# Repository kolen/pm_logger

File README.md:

# Firmware

## Building firmware

* Install [platformio](https://platformio.org)
* Run `pio run` in root dir

To flash firmware:

* Run `pio run -t upload`

## Running tests

* Install native C++ toolchain (for your system, not for cross-compilation), clang or gcc
* Install [meson](https://mesonbuild.com/) build system and [ninja](https://ninja-build.org/) low-level build system
* Run `meson builddir` in the root directory of project
* Change dir to `builddir` and run `ninja test`

## Using native simulator

Native simulator runs on unix-like systems. It runs the same main loop
as actual app and has networking, but instead of real sensor readings,
it reads the same value each time. Simulated time is 60x faster that
real time, i.e. each simulated hour is a real minute.

To build native simulator, use the same steps as for tests, but just
run `ninja`. It builds `pm_sensor_fake` executable in `builddir`.

# Logging node

## Building and installing

* Install Rust and Cargo
* Run `cargo build` in `logging_node` directory
* Install [Diesel](http://diesel.rs/) cli: `cargo install diesel_cli
  --no-default-features --features sqlite` (by default, all features
  are installed, which require client libs for postgresql and mysql,
  which are not needed for logging node)
* Run schema migration: `diesel migration run`
* Run built binary directly or with `cargo run`

# Homebridge plugin

## Installing

* Install node.js
* Install and configure [homebridge](https://github.com/nfarina/homebridge)
* Run `npm install -g` in `homebridge-pm-sensor` dir
* Add accessory to homebridge:

  ```json
      "accessories": [
          {
              "accessory": "PMSensor",
              "name": "pm_sensor"
          }
      ]
  ```

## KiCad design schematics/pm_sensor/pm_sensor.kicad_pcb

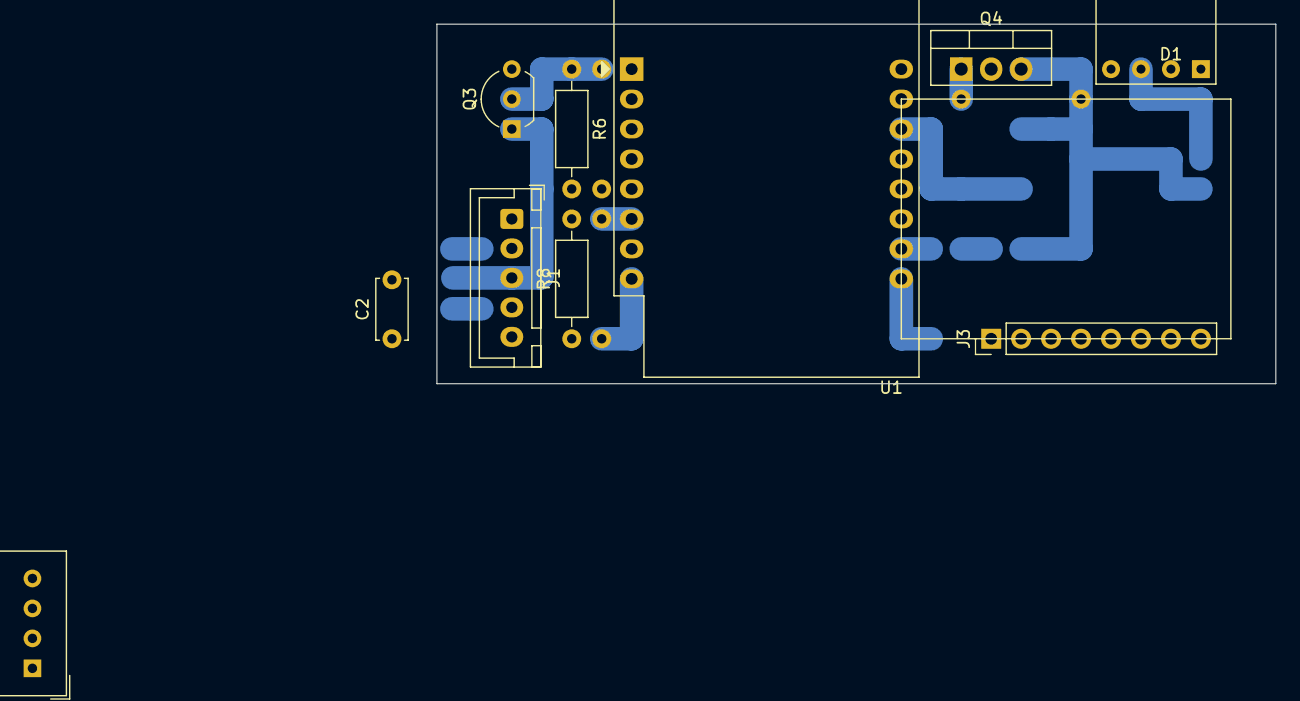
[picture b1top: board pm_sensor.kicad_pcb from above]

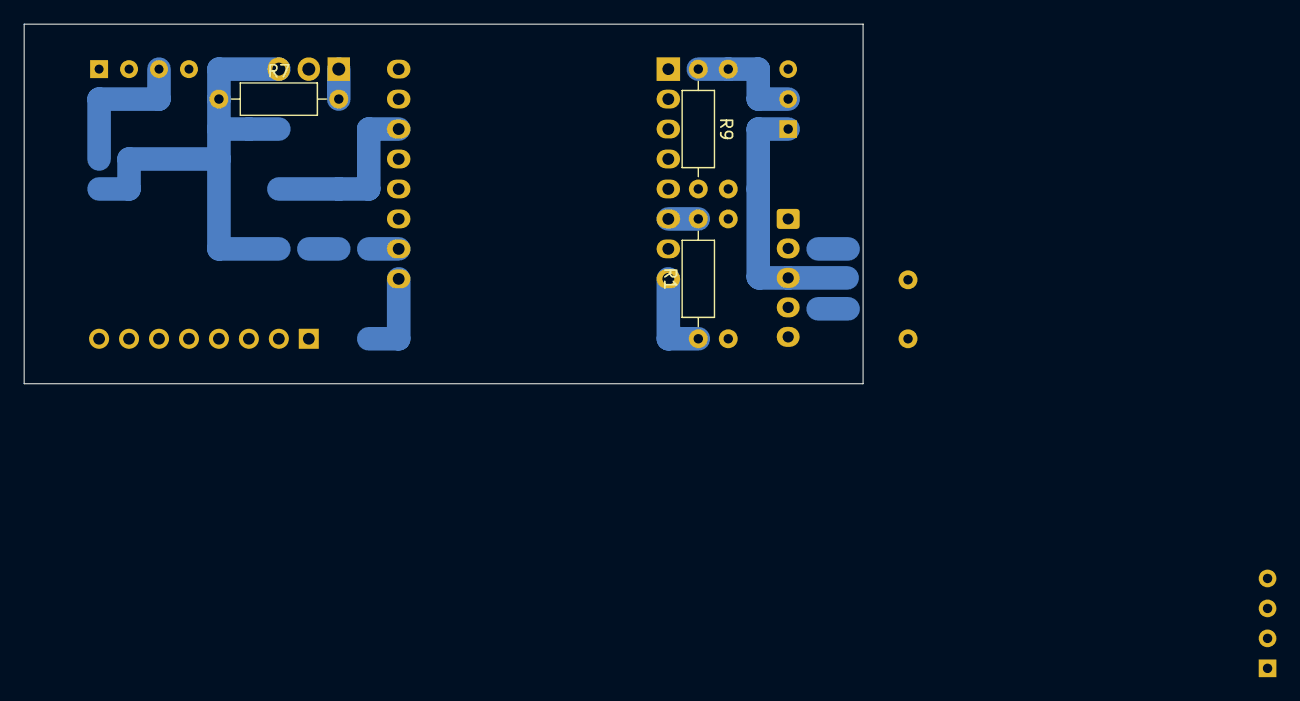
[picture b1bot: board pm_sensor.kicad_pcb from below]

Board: 2 copper layers, 71.1 x 30.5 mm, 13 parts (3 on the bottom side), 14 nets.

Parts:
C2: 100nF; C_Disc_D5.0mm_W2.5mm_P5.00mm
D1: BMP180_breakout; BMP180_Breakout
J1: sds011_conn; JST_XH_B5B-XH-A_1x05_P2.50mm_Vertical
J3: display_conn; PinHeader_1x08_P2.54mm_Vertical
Q3: 2N7000TA; TO-92_Inline_Wide
Q4: IRF9510; TO-220-3_Vertical
R1, R7, R9: 10k; R_Axial_DIN0207_L6.3mm_D2.5mm_P10.16mm_Horizontal
R6, R8: 300; R_Axial_DIN0207_L6.3mm_D2.5mm_P10.16mm_Horizontal
U1: WeMos_D1_mini; WEMOS_D1_mini_light
U2: DHT22; Aosong_DHT11_5.5x12.0_P2.54mm

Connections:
+3V3: D1.4, J3.6, R1.1, U1.8, U2.1
+5V: Q4.3, R7.1, U1.9
GND: C2.2, D1.3, J1.3, J3.2, J3.8, Q3.1, R9.2, U1.10, U2.4
unnamed: Q3.2, R6.1, R9.1
unnamed: Q3.3, R8.2
unnamed: Q4.1, R7.2, R8.1
dht_data: R1.2, U1.6, U2.2
rst: J3.1, U1.1
scl_3v: D1.2, U1.13
sda_3v: D1.1, U1.14
sds_rx: J1.1, U1.4
sds_switch: R6.2, U1.3
sds_tx: J1.2, U1.5
sds_vcc: C2.1, J1.4, Q4.2

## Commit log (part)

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2019-03-24 Fix matching in Display impl for QueryCharacteristic
2019-03-24 Add LOGGER_HOST to .env
2019-03-26 Add homebridge module
2019-04-01 Return result from update_characteristic
2019-05-20 Add schematics
2019-05-20 Bump container version in circleci
2019-05-21 Add delay after turning on SDS011 (check if necessary)
2019-06-18 Ignore fp-info-cache
2019-07-25 Build & test logging_node on CI (#19)
2019-07-25 Bump memchr from 2.2.0 to 2.2.1 in /logging_node (#18)
    Bumps [memchr](https://github.com/BurntSushi/rust-memchr) from 2.2.0 to 2.2.1.
    - [Release notes](https://github.com/BurntSushi/rust-memchr/releases)
    - [Commits](https://github.com/BurntSushi/rust-memchr/compare/2.2.0...2.2.1)
2019-07-25 Bump dotenv from 0.13.0 to 0.14.1 in /logging_node (#16)
    Bumps [dotenv](https://github.com/dotenv-rs/dotenv) from 0.13.0 to 0.14.1.
    - [Release notes](https://github.com/dotenv-rs/dotenv/releases)
    - [Changelog](https://github.com/dotenv-rs/dotenv/blob/master/CHANGELOG.md)
    - [Commits](https://github.com/dotenv-rs/dotenv/compare/v0.13.0...v0.14.1)
2019-07-25 Bump byteorder from 1.3.1 to 1.3.2 in /logging_node
    Bumps [byteorder](https://github.com/BurntSushi/byteorder) from 1.3.1 to 1.3.2.
    - [Release notes](https://github.com/BurntSushi/byteorder/releases)
    - [Changelog](https://github.com/BurntSushi/byteorder/blob/master/CHANGELOG.md)
    - [Commits](https://github.com/BurntSushi/byteorder/compare/1.3.1...1.3.2)
2019-07-25 Bump autocfg from 0.1.2 to 0.1.5 in /logging_node
    Bumps [autocfg](https://github.com/cuviper/autocfg) from 0.1.2 to 0.1.5.
    - [Release notes](https://github.com/cuviper/autocfg/releases)
    - [Commits](https://github.com/cuviper/autocfg/commits)
2019-07-25 Bump syn from 0.15.29 to 0.15.42 in /logging_node (#23)
    Bumps [syn](https://github.com/dtolnay/syn) from 0.15.29 to 0.15.42.
    - [Release notes](https://github.com/dtolnay/syn/releases)
    - [Commits](https://github.com/dtolnay/syn/compare/0.15.29...0.15.42)
2019-07-25 Bump num-traits from 0.2.6 to 0.2.8 in /logging_node (#25)
    Bumps [num-traits](https://github.com/rust-num/num-traits) from 0.2.6 to 0.2.8.
    - [Release notes](https://github.com/rust-num/num-traits/releases)
    - [Changelog](https://github.com/rust-num/num-traits/blob/master/RELEASES.md)
    - [Commits](https://github.com/rust-num/num-traits/compare/num-traits-0.2.6...num-traits-0.2.8)
2019-07-25 Bump cc from 1.0.31 to 1.0.38 in /logging_node (#26)
    Bumps [cc](https://github.com/alexcrichton/cc-rs) from 1.0.31 to 1.0.38.
    - [Release notes](https://github.com/alexcrichton/cc-rs/releases)
    - [Commits](https://github.com/alexcrichton/cc-rs/compare/1.0.31...1.0.38)
2019-07-25 Bump ucd-util from 0.1.3 to 0.1.5 in /logging_node
    Bumps [ucd-util](https://github.com/BurntSushi/ucd-generate) from 0.1.3 to 0.1.5.
    - [Release notes](https://github.com/BurntSushi/ucd-generate/releases)
    - [Commits](https://github.com/BurntSushi/ucd-generate/compare/ucd-util-0.1.3...ucd-util-0.1.5)
2019-07-26 Bump num-integer from 0.1.39 to 0.1.41 in /logging_node (#31)
    Bumps [num-integer](https://github.com/rust-num/num-integer) from 0.1.39 to 0.1.41.
    - [Release notes](https://github.com/rust-num/num-integer/releases)
    - [Changelog](https://github.com/rust-num/num-integer/blob/master/RELEASES.md)
    - [Commits](https://github.com/rust-num/num-integer/compare/num-integer-0.1.39...num-integer-0.1.41)
2019-07-26 Bump synstructure from 0.10.1 to 0.10.2 in /logging_node
    Bumps [synstructure](https://github.com/mystor/synstructure) from 0.10.1 to 0.10.2.
    - [Release notes](https://github.com/mystor/synstructure/releases)
    - [Commits](https://github.com/mystor/synstructure/commits)
2019-07-29 Bump regex from 1.1.2 to 1.2.0 in /logging_node (#36)
    Bumps [regex](https://github.com/rust-lang/regex) from 1.1.2 to 1.2.0.
    - [Release notes](https://github.com/rust-lang/regex/releases)
    - [Changelog](https://github.com/rust-lang/regex/blob/master/CHANGELOG.md)
    - [Commits](https://github.com/rust-lang/regex/compare/1.1.2...1.2.0)
2019-07-29 Bump backtrace from 0.3.14 to 0.3.33 in /logging_node
    Bumps [backtrace](https://github.com/rust-lang/backtrace-rs) from 0.3.14 to 0.3.33.
    - [Release notes](https://github.com/rust-lang/backtrace-rs/releases)
    - [Commits](https://github.com/rust-lang/backtrace-rs/compare/0.3.14...0.3.33)
2019-08-05 Bump regex-syntax from 0.6.10 to 0.6.11 in /logging_node
    Bumps [regex-syntax](https://github.com/rust-lang/regex) from 0.6.10 to 0.6.11.
    - [Release notes](https://github.com/rust-lang/regex/releases)
    - [Changelog](https://github.com/rust-lang/regex/blob/master/CHANGELOG.md)
    - [Commits](https://github.com/rust-lang/regex/compare/regex-syntax-0.6.10...regex-syntax-0.6.11)
2019-08-06 Bump aho-corasick from 0.7.4 to 0.7.6 in /logging_node
    Bumps [aho-corasick](https://github.com/BurntSushi/aho-corasick) from 0.7.4 to 0.7.6.
    - [Release notes](https://github.com/BurntSushi/aho-corasick/releases)
    - [Commits](https://github.com/BurntSushi/aho-corasick/compare/0.7.4...0.7.6)
2019-08-06 Bump quote from 0.6.11 to 0.6.13 in /logging_node
    Bumps [quote](https://github.com/dtolnay/quote) from 0.6.11 to 0.6.13.
    - [Release notes](https://github.com/dtolnay/quote/releases)
    - [Commits](https://github.com/dtolnay/quote/compare/0.6.11...0.6.13)
2019-08-07 Bump log from 0.4.6 to 0.4.8 in /logging_node
    Bumps [log](https://github.com/rust-lang/log) from 0.4.6 to 0.4.8.
    - [Release notes](https://github.com/rust-lang/log/releases)
    - [Changelog](https://github.com/rust-lang-nursery/log/blob/master/CHANGELOG.md)
    - [Commits](https://github.com/rust-lang/log/commits)
2019-09-02 Bump chrono from 0.4.7 to 0.4.8 in /logging_node
    Bumps [chrono](https://github.com/chronotope/chrono) from 0.4.7 to 0.4.8.
    - [Release notes](https://github.com/chronotope/chrono/releases)
    - [Changelog](https://github.com/chronotope/chrono/blob/master/CHANGELOG.md)
    - [Commits](https://github.com/chronotope/chrono/commits)
2019-09-24 Bump env_logger from 0.6.2 to 0.7.0 in /logging_node
    Bumps [env_logger](https://github.com/sebasmagri/env_logger) from 0.6.2 to 0.7.0.
    - [Release notes](https://github.com/sebasmagri/env_logger/releases)
    - [Changelog](https://github.com/sebasmagri/env_logger/blob/master/CHANGELOG.md)
    - [Commits](https://github.com/sebasmagri/env_logger/compare/v0.6.2...v0.7.0)
2019-10-14 Require data buffer to be initialized outside, don't try to memset
2019-10-14 Bump failure from 0.1.5 to 0.1.6 in /logging_node (#55)
    Bumps [failure](https://github.com/rust-lang-nursery/failure) from 0.1.5 to 0.1.6.
    - [Release notes](https://github.com/rust-lang-nursery/failure/releases)
    - [Changelog](https://github.com/rust-lang-nursery/failure/blob/master/RELEASES.md)
    - [Commits](https://github.com/rust-lang-nursery/failure/commits)
2019-10-22 Bump env_logger from 0.7.0 to 0.7.1 in /logging_node (#57)
    Bumps [env_logger](https://github.com/sebasmagri/env_logger) from 0.7.0 to 0.7.1.
    - [Release notes](https://github.com/sebasmagri/env_logger/releases)
    - [Changelog](https://github.com/sebasmagri/env_logger/blob/master/CHANGELOG.md)
    - [Commits](https://github.com/sebasmagri/env_logger/compare/v0.7.0...v0.7.1)
2019-10-28 Some unknown schematic changes [skip ci]
2019-11-03 Remove 'bmp' member when compiled not for arduino
2019-11-03 Update deprecated env_default to default_envs
2019-11-03 logging_node: Add Pressure to requested characteristics
2019-11-04 logging_node: Remove unnecessary String::from
2019-12-02 Update packet size for current data
2019-12-12 Add Cayenne
2019-12-17 Add refresh functionality
2019-12-18 Fix buildability after adding Cayenne
2019-12-18 Add DATABASE_URL env var to logging_node started by chart_server
2019-12-20 Wrap update of characteristics in exclusive transaction
2019-12-20 Defer computing string when doing connection
2019-12-23 Fix flash memory address offset
2019-12-23 Use stm32fxx_hal and stm32f103 crate from pac exported from it
2019-12-23 Tweak dev profile
    (still problems with Dwarf Error: Cannot find DIE at 0x3cbc referenced
    from DIE at 0x2b26)
2019-12-24 Run measurement every 10 seconds
2019-12-25 Trim reference to imported type
2020-03-21 Add missing semicolon
2020-03-21 Add rackup config for chart_server [skip ci]
2020-03-27 Bump diesel from 1.4.3 to 1.4.4 in /logging_node (#66)
    Bumps [diesel](https://github.com/diesel-rs/diesel) from 1.4.3 to 1.4.4.
    - [Release notes](https://github.com/diesel-rs/diesel/releases)
    - [Changelog](https://github.com/diesel-rs/diesel/blob/v1.4.4/CHANGELOG.md)
    - [Commits](https://github.com/diesel-rs/diesel/compare/v1.4.3...v1.4.4)
2020-04-01 Extract shitty_delay to its own module
2020-05-16 Add request_response
2020-05-16 Add query method
2020-05-17 Enable logging in chart_server
2020-05-17 Add periodic measuring of CO2
2020-05-18 Extract mh-z-rr and -request-response to crates
2020-05-19 Add assertion to test
2020-05-21 Add fails to simulated read and write
2020-05-31 Disable loading in gdbinit (load manually)
2020-05-31 Add reading before initializing device
2020-06-02 Use SPI for display
2020-06-04 Ignore serial errors, making equivalent to garbage
2020-06-07 Update formatting on display
2020-06-07 Fix buffer not large enough for formatted text
2020-06-10 Bump chrono from 0.4.10 to 0.4.11 in /logging_node
    Bumps [chrono](https://github.com/chronotope/chrono) from 0.4.10 to 0.4.11.
    - [Release notes](https://github.com/chronotope/chrono/releases)
    - [Changelog](https://github.com/chronotope/chrono/blob/master/CHANGELOG.md)
    - [Commits](https://github.com/chronotope/chrono/compare/v0.4.10...v0.4.11)
2020-06-10 Bump byteorder from 1.3.2 to 1.3.4 in /logging_node
    Bumps [byteorder](https://github.com/BurntSushi/byteorder) from 1.3.2 to 1.3.4.
    - [Release notes](https://github.com/BurntSushi/byteorder/releases)
    - [Changelog](https://github.com/BurntSushi/byteorder/blob/master/CHANGELOG.md)
    - [Commits](https://github.com/BurntSushi/byteorder/compare/1.3.2...1.3.4)
2020-06-28 Add measurements_store module (wip)
2020-07-04 Make constants uppercased
2020-07-07 Bump chrono from 0.4.12 to 0.4.13 in /logging_node
    (#70)
    Bumps [chrono](https://github.com/chronotope/chrono) from 0.4.12 to 0.4.13.
    - [Release notes](https://github.com/chronotope/chrono/releases)
    - [Changelog](https://github.com/chronotope/chrono/blob/master/CHANGELOG.md)
    - [Commits](https://github.com/chronotope/chrono/compare/v0.4.12...v0.4.13)
2020-09-29 Add to_influxdb script
2020-10-27 Comment out check for flushed lock
2020-12-01 Update circleci docker image
2020-12-01 Bump log from 0.4.8 to 0.4.11 in /logging_node
    (#71)
    Bumps [log](https://github.com/rust-lang/log) from 0.4.8 to 0.4.11.
    - [Release notes](https://github.com/rust-lang/log/releases)
    - [Changelog](https://github.com/rust-lang/log/blob/master/CHANGELOG.md)
    - [Commits](https://github.com/rust-lang/log/compare/0.4.8...0.4.11)
2021-01-12 Bump log from 0.4.12 to 0.4.13 in /logging_node
    Bumps [log](https://github.com/rust-lang/log) from 0.4.12 to 0.4.13.
    - [Release notes](https://github.com/rust-lang/log/releases)
    - [Changelog](https://github.com/rust-lang/log/blob/master/CHANGELOG.md)
    - [Commits](https://github.com/rust-lang/log/compare/0.4.12...0.4.13)
2021-03-11 Bump byteorder from 1.3.4 to 1.4.3 in /logging_node
    Bumps [byteorder](https://github.com/BurntSushi/byteorder) from 1.3.4 to 1.4.3.
    - [Release notes](https://github.com/BurntSushi/byteorder/releases)
    - [Changelog](https://github.com/BurntSushi/byteorder/blob/master/CHANGELOG.md)
    - [Commits](https://github.com/BurntSushi/byteorder/compare/1.3.4...1.4.3)
